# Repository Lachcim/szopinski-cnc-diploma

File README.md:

# szopinski-cnc-diploma

A CNC machine for drawing on flat surfaces. Have a computer draw your favorite MS Paint doodles on paper! Part of my bachelor's thesis supervised by Mr Urbański, MSc, soon-to-be PhD.  Also check out [szopinski-emisy](https://github.com/Lachcim/szopinski-emisy) for more cool microcontroller stuff.

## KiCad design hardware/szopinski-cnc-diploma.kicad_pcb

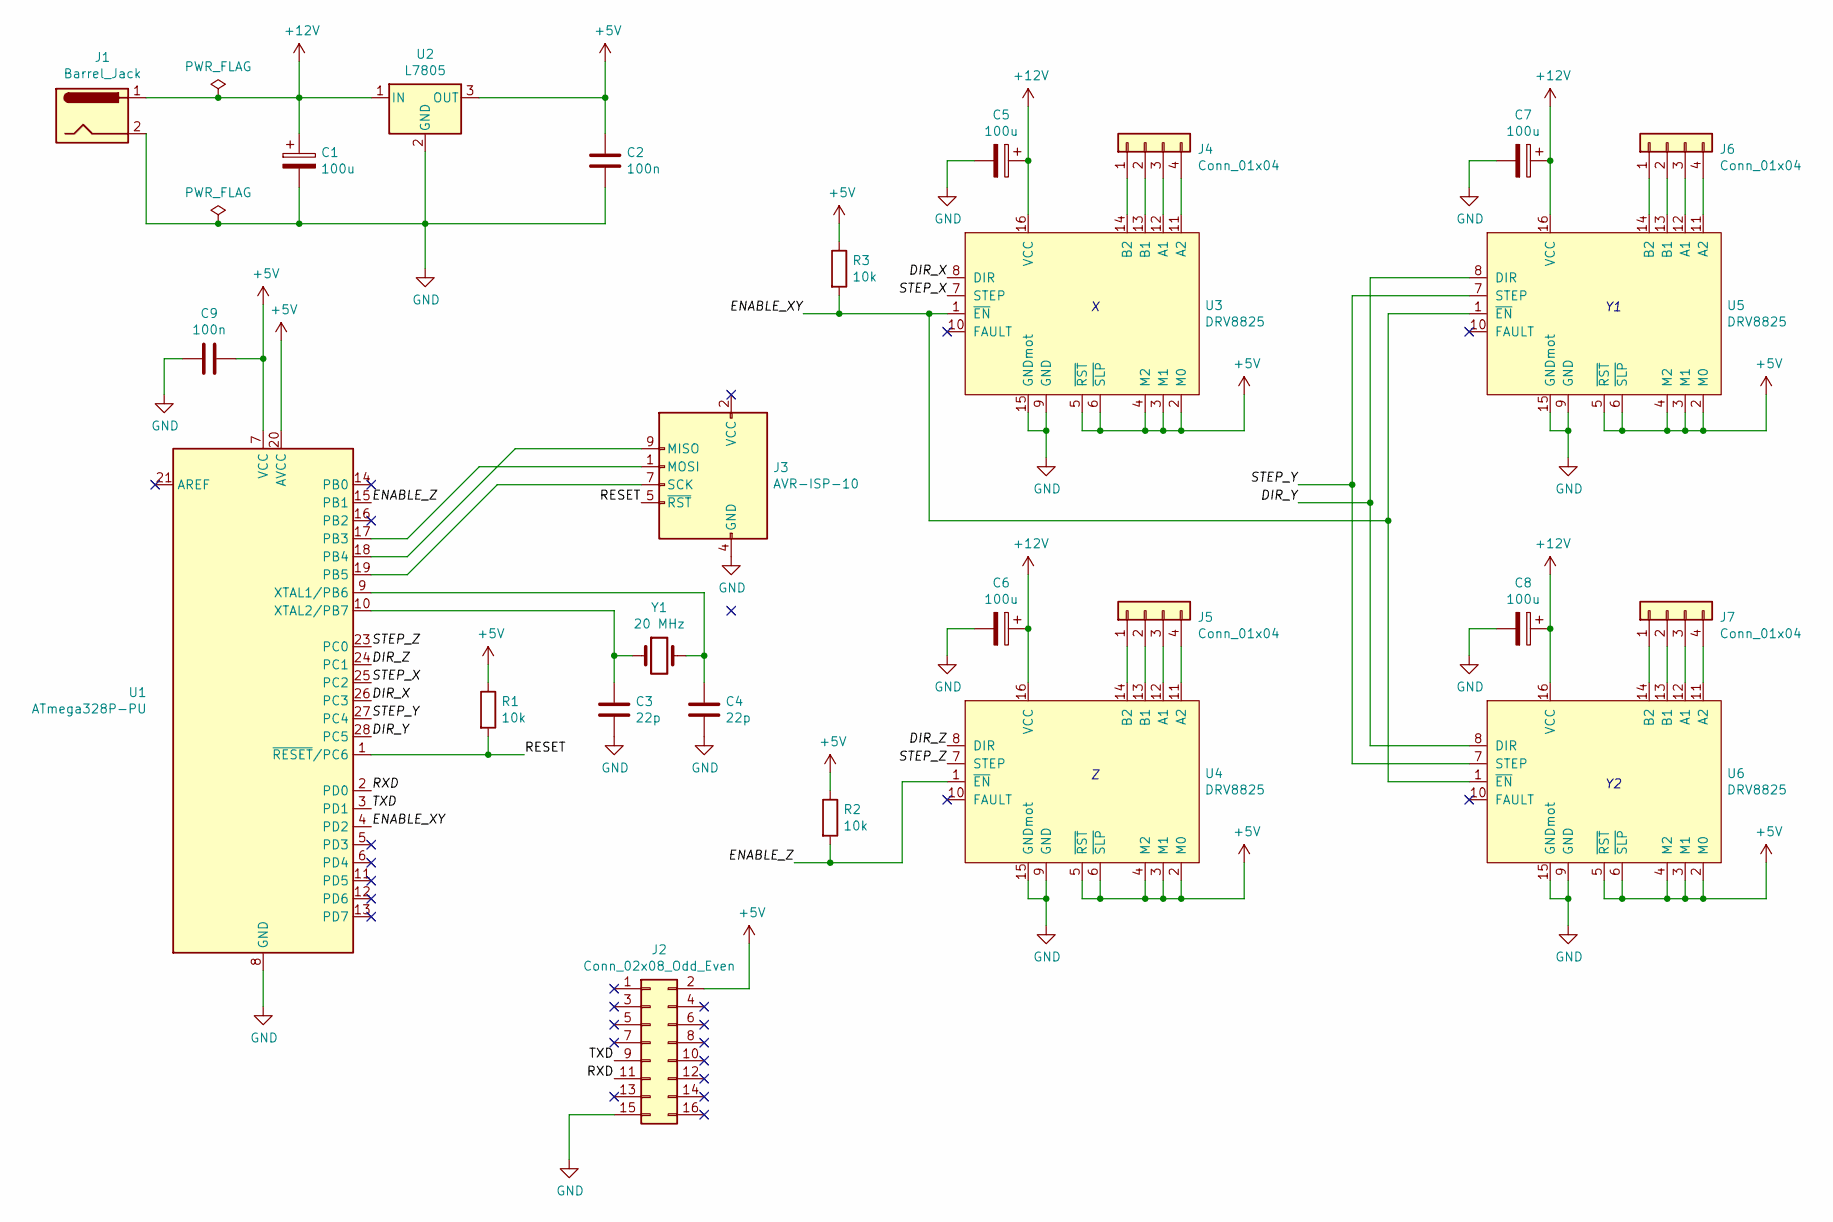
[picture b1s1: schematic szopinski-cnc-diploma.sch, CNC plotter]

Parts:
C1, C5, C6, C7, C8: 100u; CP_Radial_D6.3mm_P2.50mm
C2, C9: 100n; C_Disc_D6.0mm_W4.4mm_P5.00mm
C3, C4: 22p; C_Disc_D6.0mm_W4.4mm_P5.00mm
J1: Barrel_Jack; BarrelJack_Horizontal
J2: Conn_02x08_Odd_Even; PinSocket_2x08_P2.54mm_Vertical
J3: AVR-ISP-10; PinHeader_2x05_P2.54mm_Vertical
J4, J5, J6, J7: Conn_01x04; Molex_KK-254_AE-6410-04A_1x04_P2.54mm_Vertical
R1, R2, R3: 10k; R_Axial_DIN0207_L6.3mm_D2.5mm_P7.62mm_Horizontal
U1: ATmega328P-PU; DIP-28_W7.62mm
U2: L7805; TO-220-3_Vertical
U3, U4, U5, U6: DRV8825; DIP-16_W15.24mm
Y1: 20 MHz; Crystal_HC49-4H_Vertical

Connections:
+5V: C2.1, C9.1, J2.2, R1.1, R2.1, R3.1, U1.7 (VCC), U1.20 (AVCC), U2.3 (OUT), U3.2 (M0), U3.3 (M1), U3.4 (M2), U3.5 (~RST), U3.6 (~SLP), U4.2 (M0), U4.3 (M1), U4.4 (M2), U4.5 (~RST), U4.6 (~SLP), U5.2 (M0), U5.3 (M1), U5.4 (M2), U5.5 (~RST), U5.6 (~SLP), U6.2 (M0), U6.3 (M1), U6.4 (M2), U6.5 (~RST), U6.6 (~SLP)
+12V: C1.1, C5.1, C6.1, C7.1, C8.1, J1.1, U2.1 (IN), U3.16 (VCC), U4.16 (VCC), U5.16 (VCC), U6.16 (VCC)
/DIR_X: U1.26 (PC3), U3.8 (DIR)
/DIR_Y: U1.28 (PC5), U5.8 (DIR), U6.8 (DIR)
/DIR_Z: U1.24 (PC1), U4.8 (DIR)
/ENABLE_XY: R3.2, U1.4 (PD2), U3.1 (~EN), U5.1 (~EN), U6.1 (~EN)
/ENABLE_Z: R2.2, U1.15 (PB1), U4.1 (~EN)
/RESET: J3.5 (~RST), R1.2, U1.1 (~RESET~/PC6)
/RXD: J2.11, U1.2 (PD0)
/STEP_X: U1.25 (PC2), U3.7 (STEP)
/STEP_Y: U1.27 (PC4), U5.7 (STEP), U6.7 (STEP)
/STEP_Z: U1.23 (PC0), U4.7 (STEP)
/TXD: J2.9, U1.3 (PD1)
GND: C1.2, C2.2, C3.2, C4.2, C5.2, C6.2, C7.2, C8.2, C9.2, J1.2, J2.15, J3.4 (GND), J3.6 (GND), J3.8 (GND), J3.10 (GND), U1.8 (GND), U1.22 (GND), U2.2 (GND), U3.9 (GND), U3.15 (GNDmot), U4.9 (GND), U4.15 (GNDmot), U5.9 (GND), U5.15 (GNDmot), U6.9 (GND), U6.15 (GNDmot)
unnamed: C3.1, U1.10 (XTAL2/PB7), Y1.1
unnamed: C4.1, U1.9 (XTAL1/PB6), Y1.2
unnamed: J3.1 (MOSI), U1.17 (PB3)
unnamed: J3.7 (SCK), U1.19 (PB5)
unnamed: J3.9 (MISO), U1.18 (PB4)
unnamed: J4.1, U3.14 (B2)
unnamed: J4.2, U3.13 (B1)
unnamed: J4.3, U3.12 (A1)
unnamed: J4.4, U3.11 (A2)
unnamed: J5.1, U4.14 (B2)
unnamed: J5.2, U4.13 (B1)
unnamed: J5.3, U4.12 (A1)
unnamed: J5.4, U4.11 (A2)
unnamed: J6.1, U5.14 (B2)
unnamed: J6.2, U5.13 (B1)
unnamed: J6.3, U5.12 (A1)
unnamed: J6.4, U5.11 (A2)
unnamed: J7.1, U6.14 (B2)
unnamed: J7.2, U6.13 (B1)
unnamed: J7.3, U6.12 (A1)
unnamed: J7.4, U6.11 (A2)

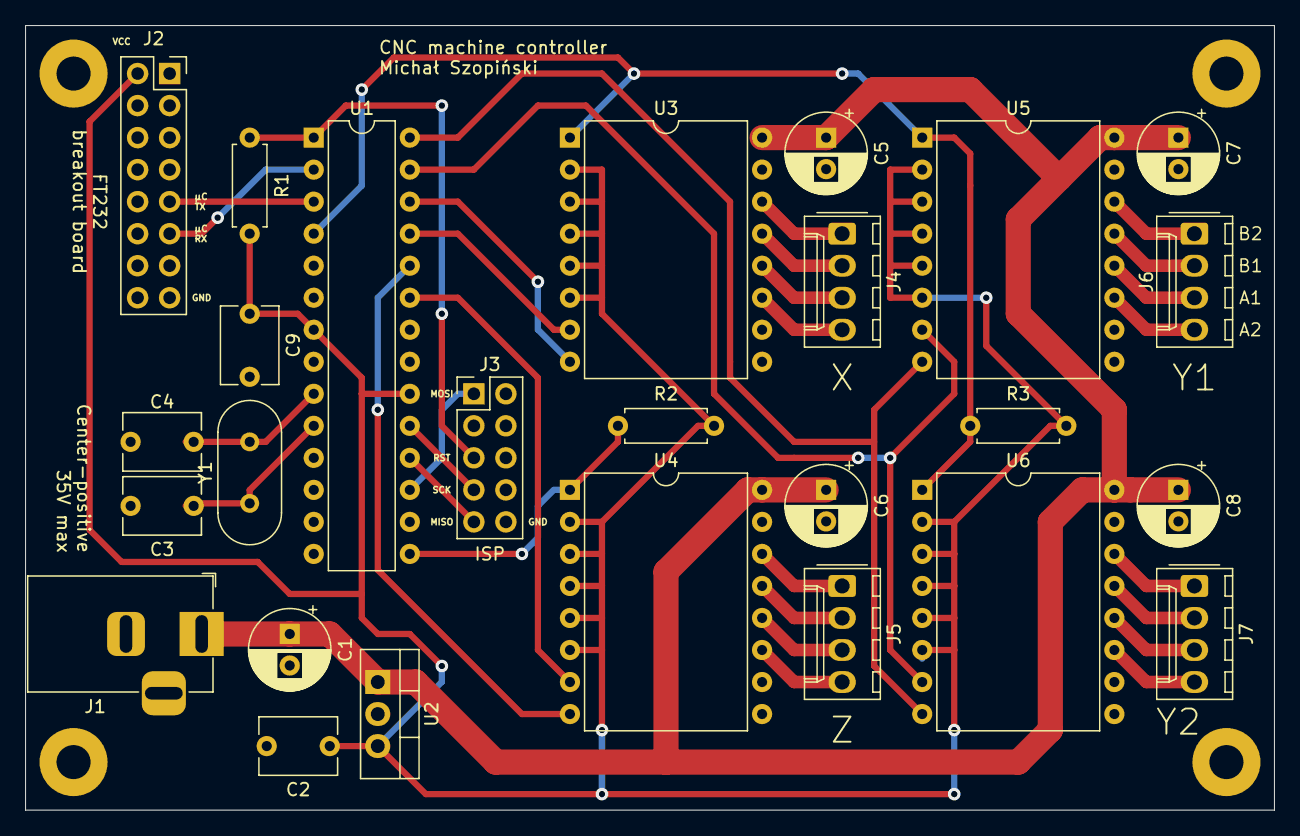
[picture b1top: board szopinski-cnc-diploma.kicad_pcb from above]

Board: 2 copper layers, 99.1 x 62.2 mm, 26 parts (0 on the bottom side), 35 nets.

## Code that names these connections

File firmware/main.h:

#ifndef MAIN_H
#define MAIN_H

#define F_CPU 20000000UL

#define DISABLE_XY PD2
#define DISABLE_XY_PORT PORTD
#define DISABLE_XY_DIR_PORT DDRD
#define DISABLE_Z PB1
#define DISABLE_Z_PORT PORTB
#define DISABLE_Z_DIR_PORT DDRB

#define STEP_PORT PORTC
#define STEP_DIR_PORT DDRC
#define X_STEP PC2
#define X_DIR PC3
#define Y_STEP PC4
#define Y_DIR PC5
#define Z_STEP PC0
#define Z_DIR PC1

#endif

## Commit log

2022-03-20 Prepare build environment
2022-03-20 Refactor entry code
2022-03-20 Add USART transmit
2022-03-20 Add USART receive
2022-03-26 Prepare command parser
2022-03-26 Add aux word assignment
2022-03-26 Handle comments and parameters
2022-03-26 Add word parsing and assignment
2022-03-26 Fix fixed-point parsing
2022-03-26 Introduce global state
2022-03-26 Add modal group assignment
2022-03-27 Refactor command parser
2022-03-27 Add non-modal support
2022-03-27 Restructure project, add execute routine
2022-03-27 Consume whitespace when reading numbers
2022-04-02 Add motion
2022-04-03 Expand command execution routine
2022-04-03 Add coordinate translation
2022-04-08 Adjust Z-axis translation
2022-04-08 Fix bug with non-motion commands
2022-04-09 Fix motion interrupt race condition
2022-04-09 Change clock speed
2022-04-09 Remove timeouts
2022-04-09 Refactor command execution
2022-04-10 Change timer configuration
2022-04-16 Add feed rate calculation
2022-04-16 Implement feed rate
2022-04-30 Remove feed rate
2022-04-30 Implement linear motion
2022-05-01 Implement receive buffer
2022-05-01 Implement variable speed
2022-05-03 Adjust motor speed
2022-05-03 Improve error handling
2022-05-03 Add feedback
2022-05-03 Change feedback delimiter
2022-05-05 Create Electron app
2022-05-05 Create LICENSE
2022-05-05 Add React
2022-05-05 Add SCSS
2022-05-05 Add status bar
2022-05-05 Add fade screen
2022-05-05 Design port selection screen
2022-05-07 Add linter
2022-05-07 Add Electron boilerplate
2022-05-07 Add serial port list
2022-05-07 Add Redux and store
2022-05-08 Restructure program, implement feedback handling
2022-05-08 Refactor state using Redux toolkit
2022-05-08 Reduce command counter to single byte
2022-05-08 Connect status bar to store
2022-05-08 Add loader
2022-05-08 Add routing and workflow screen
2022-05-08 Add error modal
2022-05-08 Improve UX smoothness
2022-05-08 Improve UI readability
2022-05-08 Split stylesheets
2022-07-10 Change loader condition
2022-07-10 Add draw preview
2022-07-12 Add CNC sender
2022-07-14 Reimplement command sending
2022-07-16 Handle partial packet
2022-07-21 Implement global command history
2022-07-24 Reimplement block deletion
2022-07-24 Remove buffer overflow error, add transmission in progress check
2022-07-24 Reimplement feedback
2022-07-24 Fix bugs in feedback and main loop
2022-07-24 Remove busy flag
2022-07-24 Prevent execution of deleted blocks
2022-07-25 Adapt to new feedback mechanism
2022-07-26 Split feedback into position and command
2022-07-26 Implement sending commands
2022-07-26 Fix race condition when sending feedback
2022-07-27 Refactor actions
2022-07-27 Implement drawing linear and rapid strokes
2022-07-28 Prepare UI to reimplement command prompt
2022-07-28 Initial implementation of command preview
2022-07-31 Add command input
2022-07-31 Improve error handling in command preview
2022-08-02 Finish command prompt
2022-08-02 Fix disconnect button
2022-08-07 Fix rapid movement drawing
2022-08-13 Add thesis template
2022-08-14 Add thesis
2022-08-15 Fix empty command on power-on
2022-08-15 Add schematic
2022-08-15 Add PCB without traces
2022-08-15 Add traces
2022-08-16 Fix footprints, symbols and clearance issues
2022-08-16 Add value for driver capacitors
2022-08-16 Redesign PCB
2022-08-16 Add custom symbol and footprint to project
2022-08-17 Reroute FT232 power
2022-08-17 Change 18V to 12V
2022-08-17 Increase input capacitor value
2022-08-17 Fix trace widths and PCB layout
2022-08-17 Fix power info on silk screen
2022-08-18 Add batch execution dropdown
2022-08-18 Separation of concerns on command prompt components
2022-08-18 Add batch execution workflow
2022-08-18 Fix dropzone
2022-08-19 Add new screen, fix CSS
2022-08-21 Add tracing - segment discovery
2022-08-21 Implement segment extension
2022-08-21 Refactor work screens
2022-08-21 Add tracing
2022-08-21 Reimplement buffer space preservation
2022-08-21 Remove buffer space information from protocol
2022-08-21 Adjustments to make tracing viable
2022-08-21 Improve visuals
2022-08-23 Improve UX for tracing
2022-08-23 Adjustments to make tracing feasible
2022-08-23 Implement negative coordinates
2022-08-23 Implement motor timeout
2022-08-23 Update packet validation
2022-08-23 Fix bug with missing interpretation
2022-08-23 Remove unimplemented functionality
2022-08-23 Prepare to add arc mode
2022-08-24 Add arc mode
2022-08-24 Protect against radius mismatch
2022-08-24 Add arc preview
2022-08-25 Fix preview for circles
2022-08-25 Fix trace draw parameters
2022-08-28 Restructure thesis
2022-08-28 Add project requirements
2022-08-29 Add hardware
2022-08-29 Start firmware
2022-08-30 Add USART and command processing
2022-08-30 Finish firmware
2022-08-30 Begin software
2022-08-31 Elaborate on software
2022-09-01 Finish motion preview
2022-09-01 Finish software
2022-09-01 Fix typos
2022-09-02 Fix bugs discovered when testing
2022-09-02 Begin tests and verification
2022-09-02 Remove debug code
2022-09-02 Finish tests
2022-09-03 Add summary
2022-09-03 Add citation, remove market analysis
2022-09-08 Add analysis
2022-09-11 Fix missing content
2022-09-12 Advisor review
2023-10-01 Add more illustrations
